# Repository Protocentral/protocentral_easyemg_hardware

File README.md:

# Protocentral easyEMG Breakout — Hardware

Open-source hardware design files for the **Protocentral easyEMG Breakout**, a single-channel surface EMG (sEMG) board on I²C / Qwiic. It's built from parts you can probe: a [TI INA333](https://www.ti.com/product/INA333) instrumentation amplifier, two [TI OPA2333](https://www.ti.com/product/OPA2333) op-amps and a [TI TLA2024](https://www.ti.com/product/TLA2024) 12-bit ADC.

Unlike an analog "muscle sensor", it outputs the **raw band-limited waveform** over I²C; the RMS envelope is computed in the library.

## Don't have one? [Buy it here](https://protocentral.com/product/easyemg-surface-emg-breakout-qwiic/)

## Links

| | |
|---|---|
| Product page | https://protocentral.com/product/easyemg-surface-emg-breakout-qwiic/ |
| Getting Started guide | https://protocentral.com/product/easyemg-surface-emg-breakout-qwiic/docs/getting-started/ |
| Arduino library | https://github.com/Protocentral/protocentral_easyemg_arduino |
| MicroPython / Raspberry Pi library | https://github.com/Protocentral/protocentral-micropython-easyemg |

## Specifications

- **Channels:** 1 surface EMG channel, 3 electrodes
- **Front end:** TI INA333 instrumentation amplifier, two TI OPA2333 op-amps, TI TLA2024 12-bit ADC
- **Gain:** ×51.7
- **Bandwidth:** about 20–310 Hz
- **Resolution:** about 2.42 µV per count at the electrodes
- **Input range:** about ±4.95 mV
- **Interface:** I²C / Qwiic, address 0x48 (0x49 via the ADDR jumper)
- **Connectors:** 2 × Qwiic / STEMMA QT, 3.5 mm electrode jack, 0.1" header
- **Supply:** 3.3 V on Qwiic; 3.3–5 V on the header
- **Board:** 40.0 × 28.8 mm

## Electrode connections

| Jack contact | Signal | Lead colour | Placement |
|---|---|---|---|
| Sleeve | **E1** | Green | muscle belly |
| Ring | **E2** | Red | muscle belly, ~20 mm from E1, along the fibres |
| Tip | **REF** | Yellow | bony landmark away from muscle: elbow or wrist |

Lead colours are for the 3-lead cable supplied in the kit.

## Repository layout

| Folder | Contents |
|---|---|
| [`hardware/`](hardware/) | KiCad project (schematic + PCB layout) and the exported [schematic PDF](hardware/protocentral-easyemg-schematic.pdf) |

## Revisions

| Revision | Date | Notes |
|---|---|---|
| v2 | 2026-10 | First release |

## Important notice

easyEMG is for research, education and evaluation only. It is **not a medical device** and has no FDA, CE or FCC approval. It has **no patient isolation**: with electrodes on a person, use a battery-powered host or an [easyISO isolated Qwiic adapter](https://protocentral.com/product/easyiso-isolated-qwiic-adapter/), and a battery-powered scope on the test points. A mains-earthed bench scope connects the person wearing the electrodes to earth.

## License

The hardware design files in this repository are licensed under the **CERN Open Hardware Licence Version 2 – Permissive (CERN-OHL-P v2)**. See [LICENSE](LICENSE).

The accompanying libraries (in the separate [protocentral_easyemg_arduino](https://github.com/Protocentral/protocentral_easyemg_arduino) and [protocentral-micropython-easyemg](https://github.com/Protocentral/protocentral-micropython-easyemg) repositories) are licensed under the MIT License.

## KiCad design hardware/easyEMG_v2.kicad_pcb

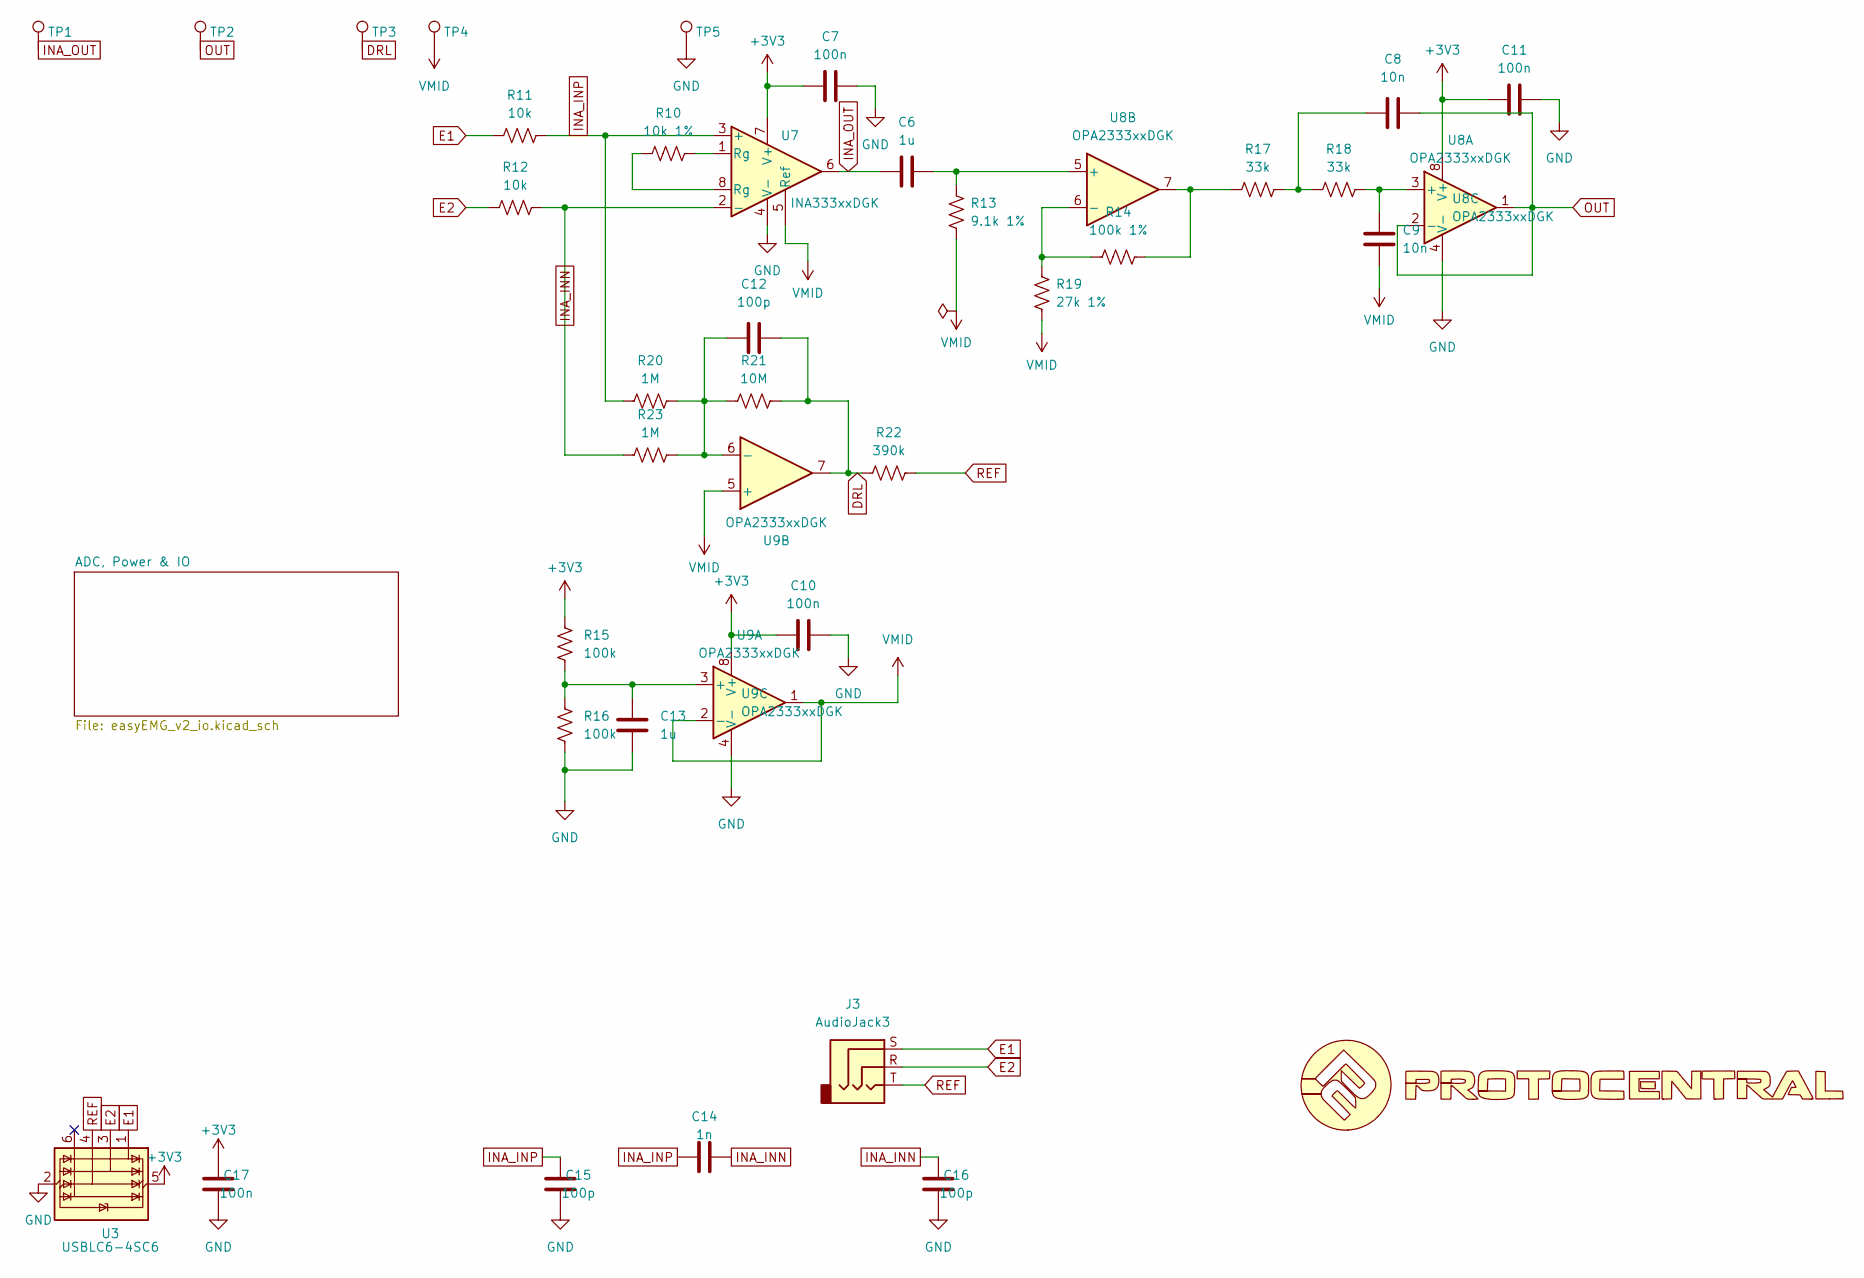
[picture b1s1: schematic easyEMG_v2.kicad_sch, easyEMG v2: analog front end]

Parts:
C6, C13: 1u; C_0402_1005Metric
C7, C10, C11, C17: 100n; C_0402_1005Metric
C8, C9: 10n; C_0402_1005Metric
C12, C15, C16: 100p; C_0402_1005Metric
C14: 1n; C_0402_1005Metric
J3: AudioJack3; Jack_3.5mm_CUI_SJ-3523-SMT_Horizontal
R10: 10k 1%; R_0402_1005Metric
R11, R12: 10k; R_0402_1005Metric
R13: 9.1k 1%; R_0402_1005Metric
R14: 100k 1%; R_0402_1005Metric
R15, R16: 100k; R_0402_1005Metric
R17, R18: 33k; R_0402_1005Metric
R19: 27k 1%; R_0402_1005Metric
R20, R23: 1M; R_0402_1005Metric
R21: 10M; R_0402_1005Metric
R22: 390k; R_0402_1005Metric
TP1: INA_OUT; TestPoint_Pad_D1.0mm
TP2: OUT; TestPoint_Pad_D1.0mm
TP3: DRL; TestPoint_Pad_D1.0mm
TP4: VMID; TestPoint_Pad_D1.0mm
TP5: GND; TestPoint_THTPad_D1.5mm_Drill0.7mm
U3: USBLC6-4SC6; SOT-23-6
U6: LOGO
U7: INA333xxDGK; VSSOP-8_3x3mm_P0.65mm
U8, U9: OPA2333xxDGK; VSSOP-8_3x3mm_P0.65mm

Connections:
+3V3: C7.2, C10.2, C11.2, C17.1, R15.1, U3.5 (VBUS), U7.7 (V+), U8.8 (V+), U9.8 (V+); also elsewhere on the board
DRL: C12.1, R21.2, R22.1, TP3.1 (1_1), U9.7; also elsewhere on the board
E1: J3.S, R11.1, U3.1 (I/O1)
E2: J3.R, R12.1, U3.3 (I/O2)
GND: C7.1, C10.1, C11.1, C13.2, C15.2, C16.2, C17.2, R16.2, TP5.1 (1_1), U3.2 (GND), U7.4 (V-), U8.4 (V-), U9.4 (V-); also elsewhere on the board
INA_INN: C14.2, C16.1, R12.2, R23.1, U7.2 (-)
INA_INP: C14.1, C15.1, R11.2, R20.1, U7.3 (+)
INA_OUT: C6.2, TP1.1 (1_1), U7.6; also elsewhere on the board
unnamed: C8.2, R17.1, R18.2
unnamed: R10.1, U7.8 (Rg)
unnamed: R10.2, U7.1 (Rg)
unnamed: R14.1, R17.2, U8.7
unnamed: C9.1, R18.1, U8.3 (+)
unnamed: C6.1, R13.2, U8.5 (+)
unnamed: R14.2, R19.1, U8.6 (-)
unnamed: C13.1, R15.2, R16.1, U9.3 (+)
unnamed: C12.2, R20.2, R21.1, R23.2, U9.6 (-)
OUT: C8.1, TP2.1 (1_1), U8.1, U8.2 (-); also elsewhere on the board
REF: J3.T, R22.2, U3.4 (I/O3)
VMID: C9.2, R13.1, R19.2, TP4.1 (1_1), U7.5 (Ref), U9.1, U9.2 (-), U9.5 (+); also elsewhere on the board

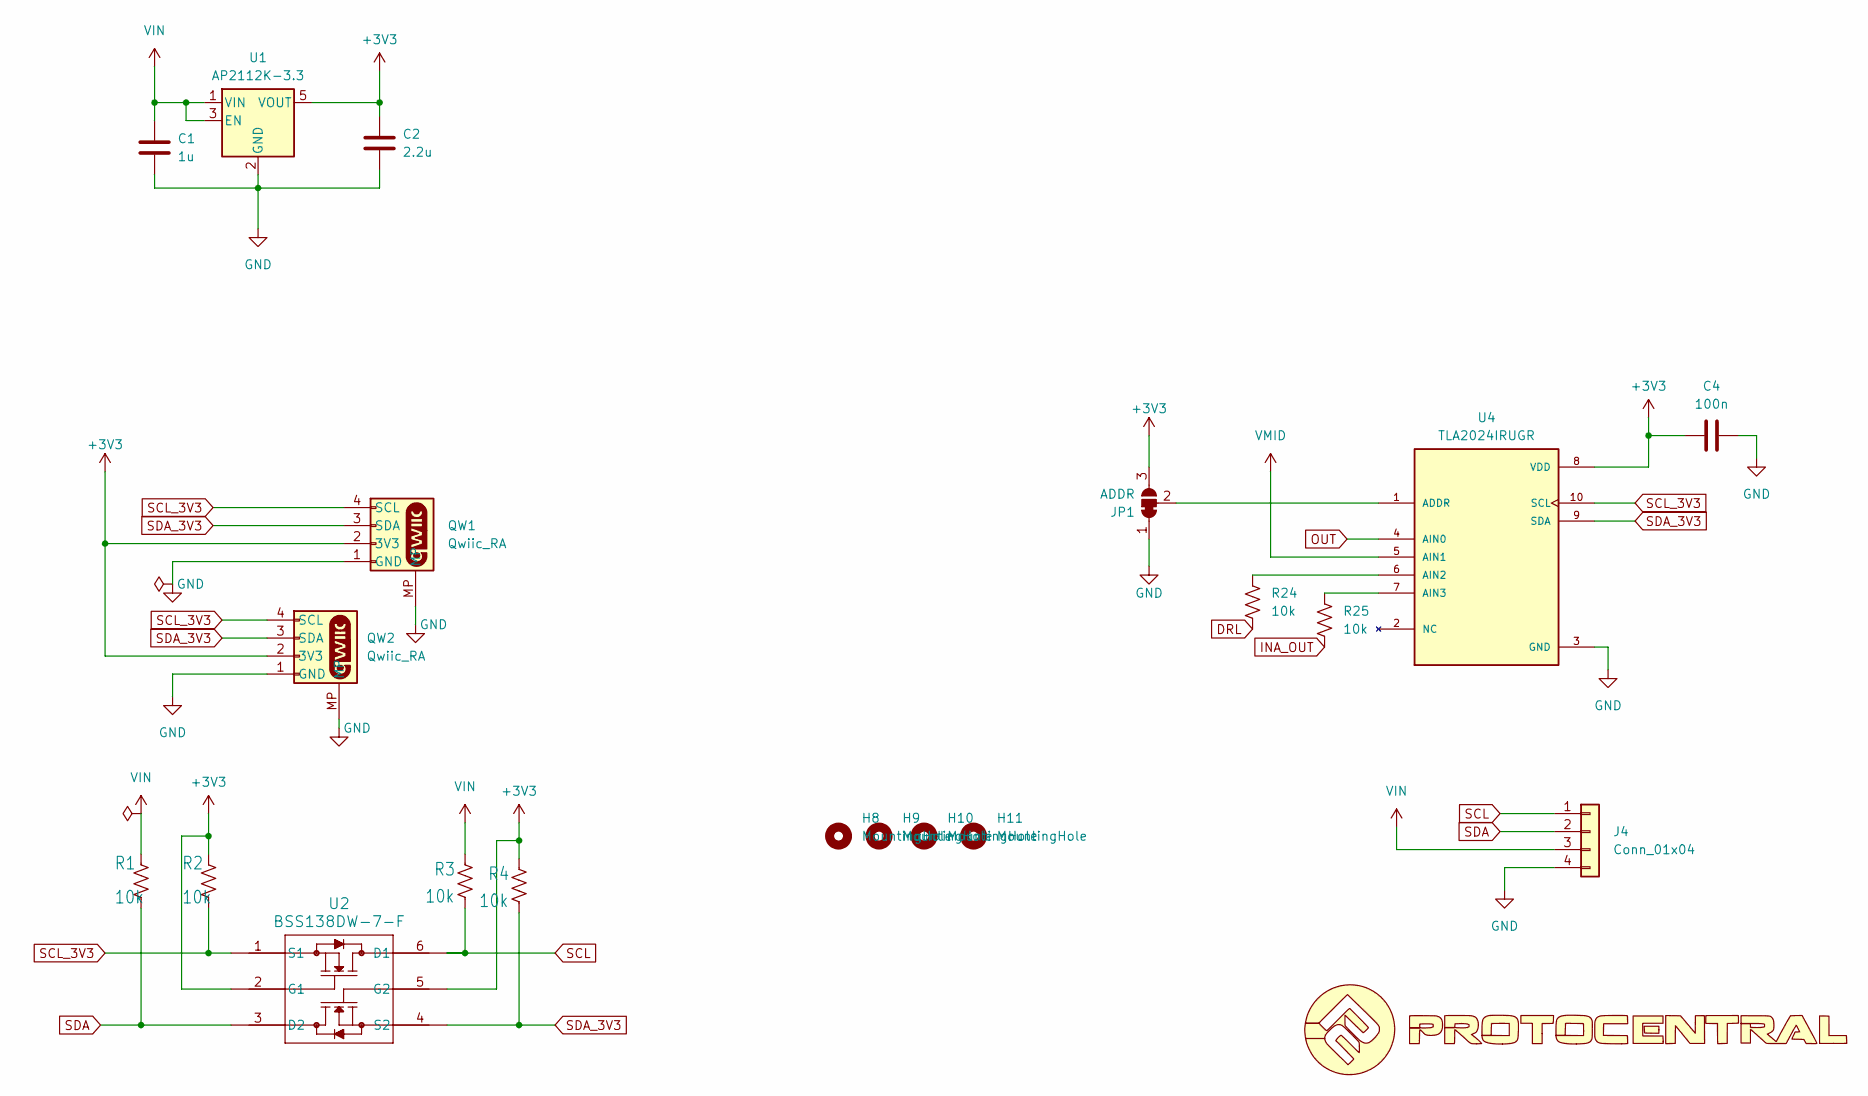
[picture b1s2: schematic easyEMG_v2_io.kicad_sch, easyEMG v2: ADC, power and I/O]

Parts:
C1: 1u; C_0402_1005Metric
C2: 2.2u; C_0402_1005Metric
C4: 100n; C_0402_1005Metric
H8, H9, H10, H11: MountingHole; MountingHole_2.2mm_M2
J4: Conn_01x04; PinHeader_1x04_P2.54mm_Vertical
JP1: ADDR; SolderJumper-3_P1.3mm_Bridged12_RoundedPad1.0x1.5mm
QW1, QW2: Qwiic_RA; JST_SH_SM04B-SRSS-TB_1x04-1MP_P1.00mm_Horizontal
R1, R2, R3, R4, R24, R25: 10k; R_0402_1005Metric
U1: AP2112K-3.3; SOT-23-5
U2: BSS138DW-7-F; SOT-363_SC-70-6
U4: TLA2024IRUGR; IC_TLA2024IRUGR; PARTREV November 2017

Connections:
+3V3: C2.1, C4.2, JP1.3 (B), QW1.2 (3V3), QW2.2 (3V3), R2.1, R4.1, U1.5 (VOUT), U2.2 (G1), U2.5 (G2), U4.8 (VDD); also elsewhere on the board
DRL: R24.2; also elsewhere on the board
GND: C1.2, C2.2, C4.1, J4.4, JP1.1 (A), QW1.1 (GND), QW1.MP, QW2.1 (GND), QW2.MP, U1.2 (GND), U4.3 (GND); also elsewhere on the board
INA_OUT: R25.2; also elsewhere on the board
unnamed: JP1.2 (C), U4.1 (ADDR)
unnamed: R24.1, U4.6 (AIN2)
unnamed: R25.1, U4.7 (AIN3)
OUT: U4.4 (AIN0); also elsewhere on the board
SCL: J4.1, R3.2, U2.6 (D1)
SCL_3V3: QW1.4 (SCL), QW2.4 (SCL), R2.2, U2.1 (S1), U4.10 (SCL)
SDA: J4.2, R1.2, U2.3 (D2)
SDA_3V3: QW1.3 (SDA), QW2.3 (SDA), R4.2, U2.4 (S2), U4.9 (SDA)
VIN: C1.1, J4.3, R1.1, R3.1, U1.1 (VIN), U1.3 (EN)
VMID: U4.5 (AIN1); also elsewhere on the board

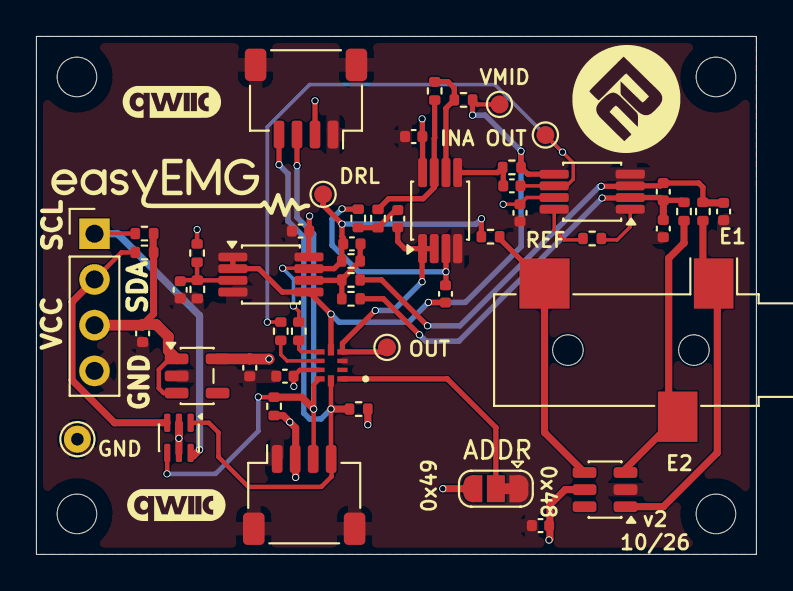
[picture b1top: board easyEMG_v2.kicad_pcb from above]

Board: 2 copper layers, 40.0 x 28.8 mm, 56 parts (0 on the bottom side), 28 nets.
